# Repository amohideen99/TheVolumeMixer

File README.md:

# The Volume Mixer
physically control the volume of your applications

### Features
- four different knobs settable to any applications
- RGB LED bar indication for volume
- 2.8 Watts/channel integrated Class D Speaker Amp
- data and power over single USB
- runs Arduino as Metro M0 Express

### Default Application Settings
```
 Knob 1 - Main Volume
 Knob 2 - Google Chrome
 Knob 3 - Discord && Spotify
 Knob 4 - CS:GO && Valorant
 ```

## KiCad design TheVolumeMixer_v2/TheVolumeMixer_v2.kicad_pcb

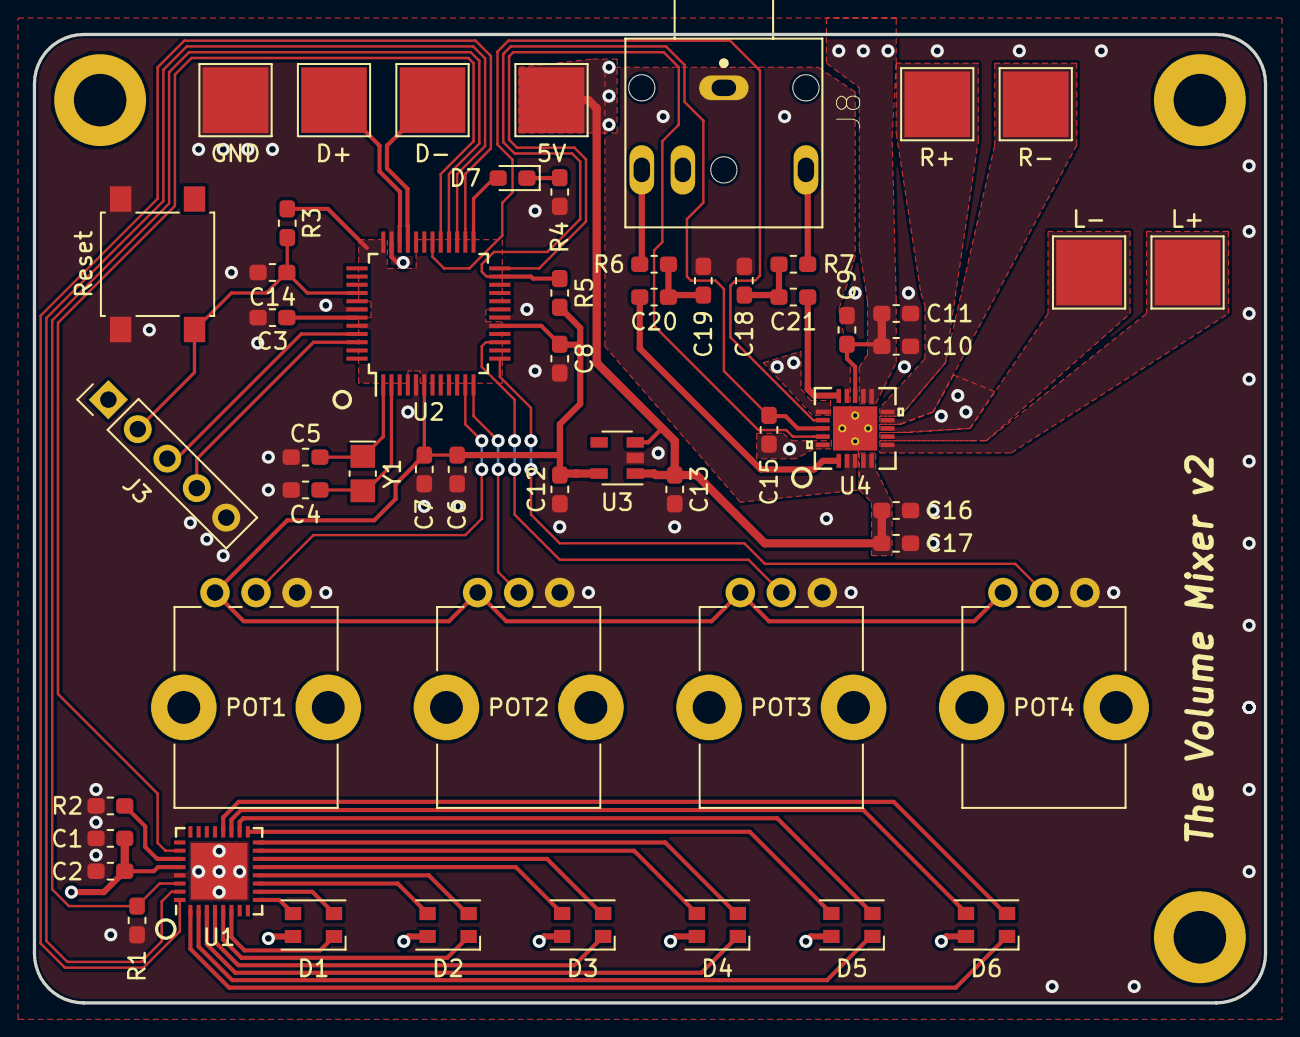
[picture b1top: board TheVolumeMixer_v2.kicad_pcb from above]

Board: 2 copper layers, 75.0 x 59.0 mm, 58 parts (0 on the bottom side), 54 nets.

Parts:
5V: Conn_01x01_Male; TestPoint_Pad_4.0x4.0mm
C1, C6, C8, C9, C10, C14, C15, C16: 0.1uF; C_0603_1608Metric_Pad1.05x0.95mm_HandSolder
C2, C3, C7, C11, C12, C13, C17, C20, C21: 1uF; C_0603_1608Metric_Pad1.05x0.95mm_HandSolder
C4, C5: 22pF; C_0603_1608Metric_Pad1.05x0.95mm_HandSolder
C18, C19: 0.047uF; C_0603_1608Metric_Pad1.05x0.95mm_HandSolder
D1, D2, D3, D4, D5, D6: LED_RGBA; LED_Cree-PLCC4_3.2x2.8mm_CCW
D7: LED; LED_0603_1608Metric_Pad1.05x0.95mm_HandSolder
D+: Conn_01x01_Male; TestPoint_Pad_4.0x4.0mm
D-: Conn_01x01_Male; TestPoint_Pad_4.0x4.0mm
GND: Conn_01x01_Male; TestPoint_Pad_4.0x4.0mm
J3: Conn_01x05; PinHeader_1x05_P2.54mm_Vertical
J8: SJ1-3544; CUI_SJ1-3544
L+: Conn_01x01_Male; TestPoint_Pad_4.0x4.0mm
L-: Conn_01x01_Male; TestPoint_Pad_4.0x4.0mm
MH1, MH2, MH3: MountingHole; MountingHole_3.2mm_M3_DIN965_Pad
POT1, POT2, POT3, POT4: R_POT_US; Potentiometer_Bourns_PTV09A-1_Single_Vertical
R1, R3: 10k; R_0603_1608Metric_Pad1.05x0.95mm_HandSolder
R2: 3.3k; R_0603_1608Metric_Pad1.05x0.95mm_HandSolder
R4: 2.2k; R_0603_1608Metric_Pad1.05x0.95mm_HandSolder
R5: 100k; R_0603_1608Metric_Pad1.05x0.95mm_HandSolder
R6, R7: 100; R_0603_1608Metric_Pad1.05x0.95mm_HandSolder
R+: Conn_01x01_Male; TestPoint_Pad_4.0x4.0mm
R-: Conn_01x01_Male; TestPoint_Pad_4.0x4.0mm
Reset: SW_Push; SW_SPST_B3S-1000
U1: TLC5947RHB; QFN-32-1EP_5x5mm_P0.5mm_EP3.45x3.45mm
U2: ATSAMD21G18A-A; TQFP-48_7x7mm_P0.5mm
U3: AP2127K-3.3; SOT-23-5
U4: TPA2017D2RTJR
Y1: 32.768kHz; Crystal_SMD_MicroCrystal_CC8V-T1A-2Pin_2.0x1.2mm_HandSolder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

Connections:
+3V3: C6.1, C7.1, C8.2, C12.2, POT1.1, POT2.1, POT3.1, POT4.1, R3.1, R5.2, U2.6, U2.17, U2.36, U2.44, U3.5
+5V: 5V.1, C1.1, C2.2, C9.1, C10.1, C11.1, C13.2, C16.1, C17.1, D1.4, D2.4, D3.4, D4.4, D5.4, D6.4, J3.1, U1.28, U3.1, U3.3, U4.4, U4.5, U4.11, U4.12, U4.13
/D1_B: D1.3, U1.9
/D1_G: D1.2, U1.10
/D1_R: D1.1, U1.6
/D2_B: D2.3, U1.11
/D2_G: D2.2, U1.12
/D2_LED: D7.2, U2.25
/D2_R: D2.1, U1.5
/D3_B: D3.3, U1.13
/D3_G: D3.2, U1.14
/D3_R: D3.1, U1.4
/D4_B: D4.3, U1.15
/D4_G: D4.2, U1.16
/D4_R: D4.1, U1.3
/D5_B: D5.3, U1.17
/D5_G: D5.2, U1.18
/D5_R: D5.1, U1.2
/D6_B: D6.3, U1.19
/D6_G: D6.2, U1.20
/D6_R: D6.1, U1.1
/EN: C15.1, R5.1, U2.23, U4.18
/INL+: C20.1, U4.1
/INR+: C21.1, U4.15
/LED_CLK: U1.31, U2.27
/LED_DATA: U1.32, U2.26
/LED_LATCH: U1.26, U2.29
/LED_OFF: R1.2, U1.30, U2.28
/OUTL+: L+.1, U4.6
/OUTL-: L-.1, U4.7
/OUTR+: R+.1, U4.10
/OUTR-: R-.1, U4.9
/RESET': C14.2, J3.2, R3.2, Reset.2, U2.40
/SP_GC1: U2.30, U4.17
/SP_GC2: U2.24, U4.19
/SWCLK: J3.3, U2.45
/SWDIO: J3.4, U2.46
/USB_D+: D+.1, U2.34
/USB_D-: D-.1, U2.33
/VOL1: POT1.2, U2.11
/VOL2: POT2.2, U2.12
/VOL3: POT3.2, U2.15
/VOL4: POT4.2, U2.13
GND: C1.2, C2.1, C3.2, C4.1, C5.1, C6.2, C7.2, C8.1, C9.2, C10.2, C11.2, C12.1, C13.1, C14.1, C15.2, C16.2, C17.2, GND.1, J3.5, POT1.3, POT2.3, POT3.3, POT4.3, R1.1, R2.1, R4.2, Reset.1, U1.29, U1.33, U2.5, U2.18, U2.35, U2.42, U3.2, U4.8, U4.16, U4.20
GNDA: C18.1, C19.1, J8.1, U4.2, U4.3, U4.14
unnamed: C3.1, U2.43
unnamed: C4.2, U2.2, Y1.2
unnamed: C5.2, U2.1, Y1.1
unnamed: C18.2, C21.2, R7.2
unnamed: C19.2, C20.2, R6.2
unnamed: D7.1, R4.1
unnamed: J8.2, R6.1
unnamed: J8.3, R7.1
unnamed: R2.2, U1.27

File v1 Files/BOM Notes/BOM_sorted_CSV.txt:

0.1uF,C1 C6 C8 C9 C10 C14 C15 C16,1276-6985-1-ND,,8,24
1uF,C2 C3 C7 C11 C12 C13 C17 C20 C21,1276-1943-1-ND,,9,27
9pF,C4 C5,1276-2142-1-ND,,2,6
0.047uF,C18 C19,1276-1063-1-ND,,2,6
LED_RGBA,D1 D2 D3 D4 D5 D6,CLV1A-FKB-CK1VW1DE1BB7C3C3CT-ND,,6,18
LED,D7,754-2165-1-ND,,1,3
Conn_01x01_Male,J1 J2 J4 J5 J6 J7 J9 J10,,,8,24
Conn_01x05,J3,,,1,3
SJ1-3544,J8,CP1-3544-ND,1.01,1,3
MountingHole,MH1 MH2 MH3,,,3,9
10k,R1 R3,541-10KAQCT-ND,,2,6
3.3k,R2,541-CRCW06033K30JNEBCT-ND,,1,3
2.2k,R4,541-2.2KGCT-ND,,1,3
100k,R5,541-CRCW0603100KJNEBCT-ND,,1,3
100.0,R6 R7,541-CRCW0603100RFKEBCT-ND,,2,6
R_POT_US,RV1 RV2 RV3 RV4,PTV09A-4020F-B203-ND,,4,12
SW_Push,SW1,SW415-ND,,1,3
TLC5947RHB,U1,296-48690-1-ND,,1,3
ATSAMD21G18A-A,U2,ATSAMD21G18A-AUTCT-ND,,1,3
AP2127K-3.3,U3,AP2127K-3.3TRG1DICT-ND,,1,3
TPA2017,U4,296-24395-1-ND,,1,3
32.768kHz,Y1,2195-CM8V-T1A-32.768KHZ-9PF-20PPM-TA-QCCT-ND,,1,3

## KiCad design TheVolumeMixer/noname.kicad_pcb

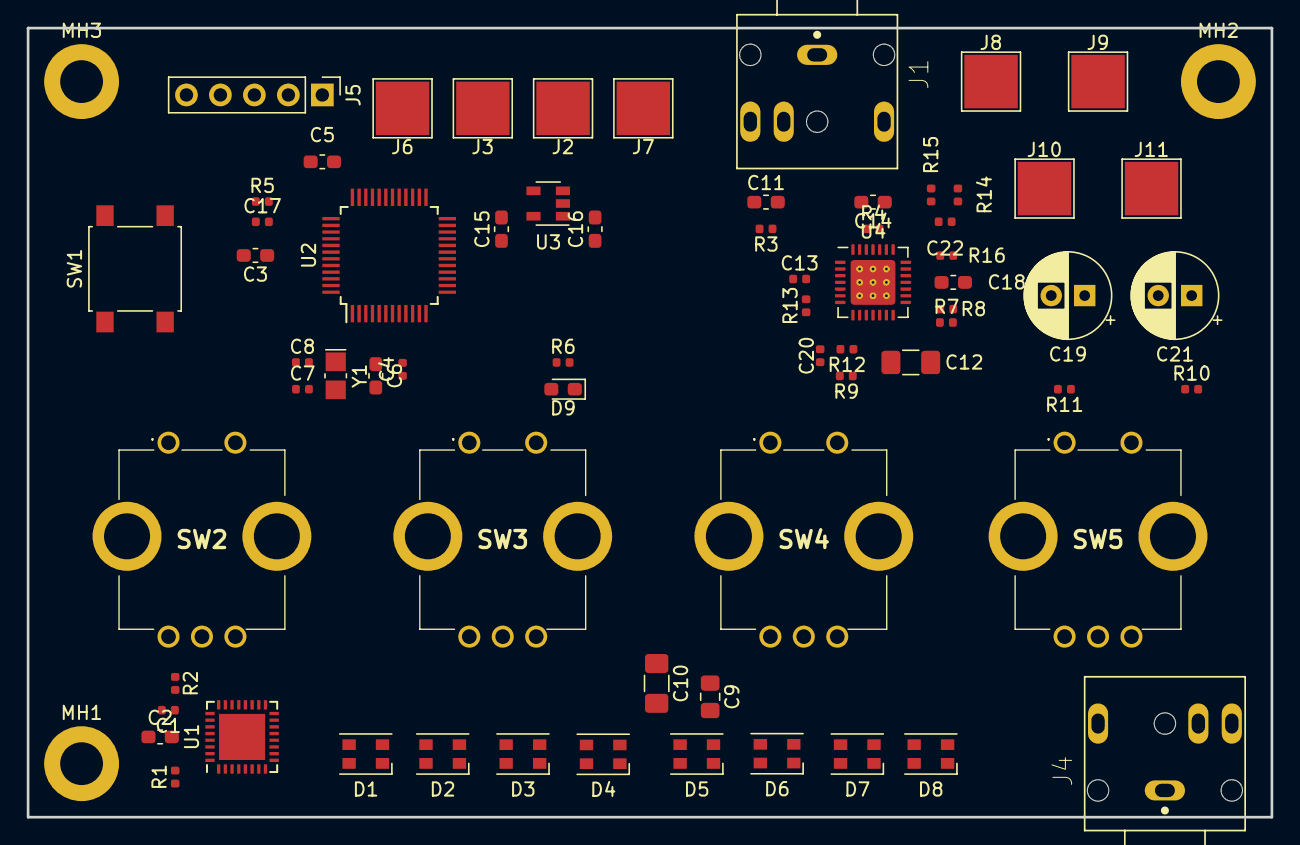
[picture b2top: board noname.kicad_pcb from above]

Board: 2 copper layers, 93.0 x 59.0 mm, 71 parts (0 on the bottom side), 72 nets, no tracks yet.

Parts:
C1, C4, C13, C17: 0.1uF; C_0402_1005Metric
C2, C3, C5, C6, C15, C16, C18: 1uF; C_0603_1608Metric_Pad1.05x0.95mm_HandSolder
C7, C8: 22pF; C_0402_1005Metric
C9: 10uF; C_0805_2012Metric_Pad1.15x1.40mm_HandSolder
C10, C12: 100uF; C_1206_3216Metric_Pad1.42x1.75mm_HandSolder
C11, C14: 0.68uF; C_0603_1608Metric_Pad1.05x0.95mm_HandSolder
C19, C21: 220uF; CP_Radial_D6.3mm_P2.50mm
C20, C22: 0.047uF; C_0402_1005Metric
D1, D2, D3, D4, D5, D6, D7, D8: LED_RGBA; LED_Cree-PLCC4_3.2x2.8mm_CCW
D9: LED; LED_0603_1608Metric_Pad1.05x0.95mm_HandSolder
J1, J4: SJ1-3544; CUI_SJ1-3544
J2, J3, J6, J7, J8, J9, J10, J11: Conn_01x01_Male; TestPoint_Pad_4.0x4.0mm
J5: Conn_01x05; PinHeader_1x05_P2.54mm_Vertical
MH1, MH2, MH3: MountingHole; MountingHole_3.2mm_M3_DIN965_Pad
R1, R5, R10, R11: 10k; R_0402_1005Metric
R2: 3.3k; R_0402_1005Metric
R3, R4, R13, R16: 15k; R_0402_1005Metric
R6: 2.2k; R_0402_1005Metric
R7: 680k; R_0402_1005Metric
R8: 47k; R_0402_1005Metric
R9, R14: 27.4k; R_0402_1005Metric
R12, R15: 33.2k; R_0402_1005Metric
SW1: SW_Push; SW_SPST_B3S-1000
SW2, SW3, SW4, SW5: Rotary_Encoder_Switch; PEC11R4220KS0024
U1: TLC5947RHB; QFN-32-1EP_5x5mm_P0.5mm_EP3.45x3.45mm
U2: ATSAMD21G18A-A; TQFP-48_7x7mm_P0.5mm
U3: AP2127K-3.3; SOT-23-5
U4: MAX9778; QFN-28-1EP_5x5mm_P0.5mm_EP3.35x3.35mm_ThermalVias
Y1: 32.768kHz; Crystal_SMD_MicroCrystal_CC8V-T1A-2Pin_2.0x1.2mm_HandSolder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

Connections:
+3V3: C4.2, C5.1, C6.1, C15.2, R5.1, U2.6, U2.17, U2.36, U2.44, U3.5
+5V: C1.1, C2.2, C9.2, C10.2, C12.2, C13.2, C16.2, D1.4, D2.4, D3.4, D4.4, D5.4, D6.4, D7.4, D8.4, J2.1, J5.1, R7.1, U1.28, U3.1, U3.3, U4.3, U4.4, U4.11, U4.25
/D1_G: D1.2, U1.2
/D1_R: D1.1, U1.1
/D2_G: D3.2, U1.5
/D2_R: D3.1, U1.4
/D3_G: D5.2, U1.8
/D3_R: D5.1, U1.7
/D4_G: D7.2, U1.11
/D4_R: D7.1, U1.10
/D5_G: D2.2, U1.14
/D5_R: D2.1, U1.13
/D6_G: D4.2, U1.17
/D6_R: D4.1, U1.16
/D7_G: D6.2, U1.20
/D7_R: D6.1, U1.19
/D8_G: D8.2, U1.23
/D8_R: D8.1, U1.22
/D13_LED: D9.2, U2.24
/GAINA': U2.19, U4.15
/GAINLA: R13.2, U4.7
/GAINLB: C20.1, R12.2, U4.8
/GAINRA: R16.2, U4.21
/GAINRB: C22.1, R15.2, U4.22
/HPS_EN: U2.20, U4.2
/IN1': U2.7, U4.28
/INL1: R3.2, U4.5
/INR1: R4.2, U4.19
/LED_CLK: U1.31, U2.12
/LED_DATA: U1.32, U2.13
/LED_LATCH: U1.26, U2.11
/LED_OFF: R1.2, U1.30, U2.10
/MUTE: U2.8, U4.1
/OUTL+: C19.1, J11.1, R9.1, R12.1, R13.1, U4.10
/OUTL-: J10.1, U4.12
/OUTR+: C21.1, J9.1, R14.1, R15.1, R16.1, U4.24
/OUTR-: J8.1, U4.26
/RESET': C17.2, J5.4, R5.2, SW1.2, U2.40
/ROT1_A: SW2.A, U2.15
/ROT1_B: SW2.B, U2.16
/ROT1_SW: SW2.S1, U2.21
/ROT2_A: SW3.A, U2.23
/ROT2_B: SW3.B, U2.25
/ROT2_SW: SW3.S1, U2.26
/ROT3_A: SW4.A, U2.27
/ROT3_B: SW4.B, U2.28
/ROT3_SW: SW4.S1, U2.29
/ROT4_A: SW5.A, U2.30
/ROT4_B: SW5.B, U2.31
/ROT4_SW: SW5.S1, U2.32
/SHDN': U2.47, U4.14
/SWCLK: J5.2, U2.45
/SWDIO: J5.3, U2.46
/TN: J4.4, R7.2, R8.2
/USB_D+: J6.1, U2.34
/USB_D-: J3.1, U2.33
GND: C1.2, C2.1, C3.2, C4.1, C5.2, C6.2, C7.1, C8.1, C9.1, C10.1, C12.1, C13.1, C15.1, C16.1, C17.1, C18.1, J1.1, J4.1, J5.5, J7.1, R1.1, R2.1, R6.2, R10.1, R11.1, SW1.1, SW2.C, SW2.S2, SW3.C, SW3.S2, SW4.C, SW4.S2, SW5.C, SW5.S2, U1.29, U1.33, U2.5, U2.18, U2.35, U2.42, U3.2, U4.6, U4.9, U4.13, U4.18, U4.20, U4.23, U4.27
unnamed: C3.1, U2.43
unnamed: C7.2, U2.2, Y1.2
unnamed: C8.2, U2.1, Y1.1
unnamed: C11.1, J1.2
unnamed: C11.2, R3.1
unnamed: C14.1, J1.3
unnamed: C14.2, R4.1
unnamed: C18.2, U4.17
unnamed: C19.2, J4.2, R10.2
unnamed: C20.2, R9.2
unnamed: C21.2, J4.3, R11.2
unnamed: C22.2, R14.2
unnamed: D9.1, R6.1
unnamed: R2.2, U1.27
unnamed: R8.1, U4.16

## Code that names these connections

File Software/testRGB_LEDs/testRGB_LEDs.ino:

#include "Adafruit_TLC5947.h"

// How many boards do you have chained?
#define NUM_TLC5974 1

#define LED_DATA   13
#define LED_CLK   10
#define LED_LATCH   6
#define LED_OFF  -1  // set to -1 to not use the enable pin (its optional)
#define D7_LED 11

Adafruit_TLC5947 tlc = Adafruit_TLC5947(NUM_TLC5974, LED_CLK, LED_DATA, LED_LATCH);

// array holding RGB LED's pin mapping
// {D1_R, D1_G, D1_B, D2_R, D2_G, D2_B, ..., D6_B}
int LED_pins[18] = {5, 9, 8, 4, 11, 10, 3, 13, 12, 2, 15, 14, 1, 17, 16, 0, 19, 18};

int R_value = 127 * 4095 / 255;
int G_value = 0 * 4095 / 255;
int B_value = 255 * 4095 / 255;

double SCALAR = 4.15;

void setup() {
  Serial.begin(9600);
  
  Serial.println("TLC5974 test");
  tlc.begin();
  if (LED_OFF >= 0) {
    pinMode(LED_OFF, OUTPUT);
    digitalWrite(LED_OFF, LOW);
  }
  //setWhite();
  pinMode(D7_LED, OUTPUT);
}

void loop() {
  SCALAR = Serial.parseFloat();
  Serial.println(SCALAR);
  digitalWrite(D7_LED, LOW);
  setWhite();
  delay(1000);
  digitalWrite(D7_LED, HIGH);
  delay(1000);
}

void setWhite() {
  
/*  int R_scaled = R_value * scalar;
  int G_scaled = G_value * scalar;
  int B_scaled = B_value * scalar;*/

  double scalar = SCALAR;
  
  for(int i = 0; i < 18; i+=3) {
    int R_val = R_value*scalar;
    int G_val = G_value*scalar;
    int B_val = B_value*scalar;
    
    tlc.setPWM(LED_pins[i],  max(0, min(1000, R_val)));
    tlc.setPWM(LED_pins[i+1], max(0, min(1000, G_val)));
    tlc.setPWM(LED_pins[i+2], max(0, min(1000, B_val)));
    scalar--;
    
  }
  tlc.write();
}

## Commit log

2021-02-13 updated readme file with qualifications
2021-02-13 came up with preliminary components chocie
2021-02-13 some components changed and Architecture Overview Diagram made
2021-02-13 editted Component selection and created KiCad project files
2021-02-14 updated Architecture, Finalized components, started on schematic
2021-02-14 finished schematic w/o Audio Amp. designated unusable pins due to Feather M0
2021-02-14 added NC's for pins not usuable as Feather M0
2021-02-14 updated ArchitectureOverview Diagram
2021-02-14 added USB data and 5V to Architecture Overview
2021-02-14 updated GPIOs for ArchitectureOverview
2021-02-14 updated Components Choice w new choices and updated reasonings
2021-02-16 Updated project sucess criteria in README. Reorganized files w datasheets and notes
2021-02-16 updated Architecture w/ new success criteria
2021-02-20 completed schematic v1, created settings doc for MAX9778
2021-02-20 schematic finished! checked once.
2021-02-21 updated libraries, finalized schematic symbols, added footprints
2021-02-21 removed unnecessary parts, started on PCB layout
2021-02-21 worked on PCB layout
2021-02-21 finalized PCB layout. added 3D shapes for most components
2021-03-03 changed pinout for MCU, replaced rotary encoders with potentiometers
2021-03-03 editted MCU pinout and capacitors
2021-03-03 directory/organizational changes
2021-03-07 changed architecture and speaker amp choice
2021-03-07 added TPA2017 to circuit diagram and made necessary net changes
2021-03-07 PCB traces MCU, Volume Knobs, and Class D Amp routed
2021-03-07 rev 1 PCB complete -- not finished
2021-03-07 created 3D preview
2021-03-09 fixed power traces for music amp, added all 3D models
2021-03-23 updated Notes and made PCB updates
2021-03-23 PCB finished, Gerbers exported
2021-03-23 made changes to SilkScreen. Regened Gerbers
2021-03-25 PCB finished, BOM created, file system reorganized
2021-05-02 Software Working Great! Enjoy!
2021-05-03 uploaded bootloaders and set improvements for Rev 3
2021-05-29 README and file system update
2021-05-29 schematic reference updates
2021-06-08 added caps for pots
2021-08-09 changed file system
2021-08-09 updated success criteria -- removed bluetooth
2021-08-09 component comparison doc created
2021-08-09 updated gitignore
2021-08-09 gitignore changes
2021-08-12 changed scaling to parabolic to give finer control at lower volumes
2021-08-12 finished v2 component selections
2021-08-12 updated success criteria
2021-08-27 editted success criteria and component specifications
2024-01-04 re-commit before starting v3
2024-01-04 created fresh v3 directories

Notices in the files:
parts and their libraries:
Copyright 2016 Accelerated Designs. All rights reserved.
